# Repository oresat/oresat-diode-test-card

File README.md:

This card tests SWIR LEDs and Photodiodes in space!

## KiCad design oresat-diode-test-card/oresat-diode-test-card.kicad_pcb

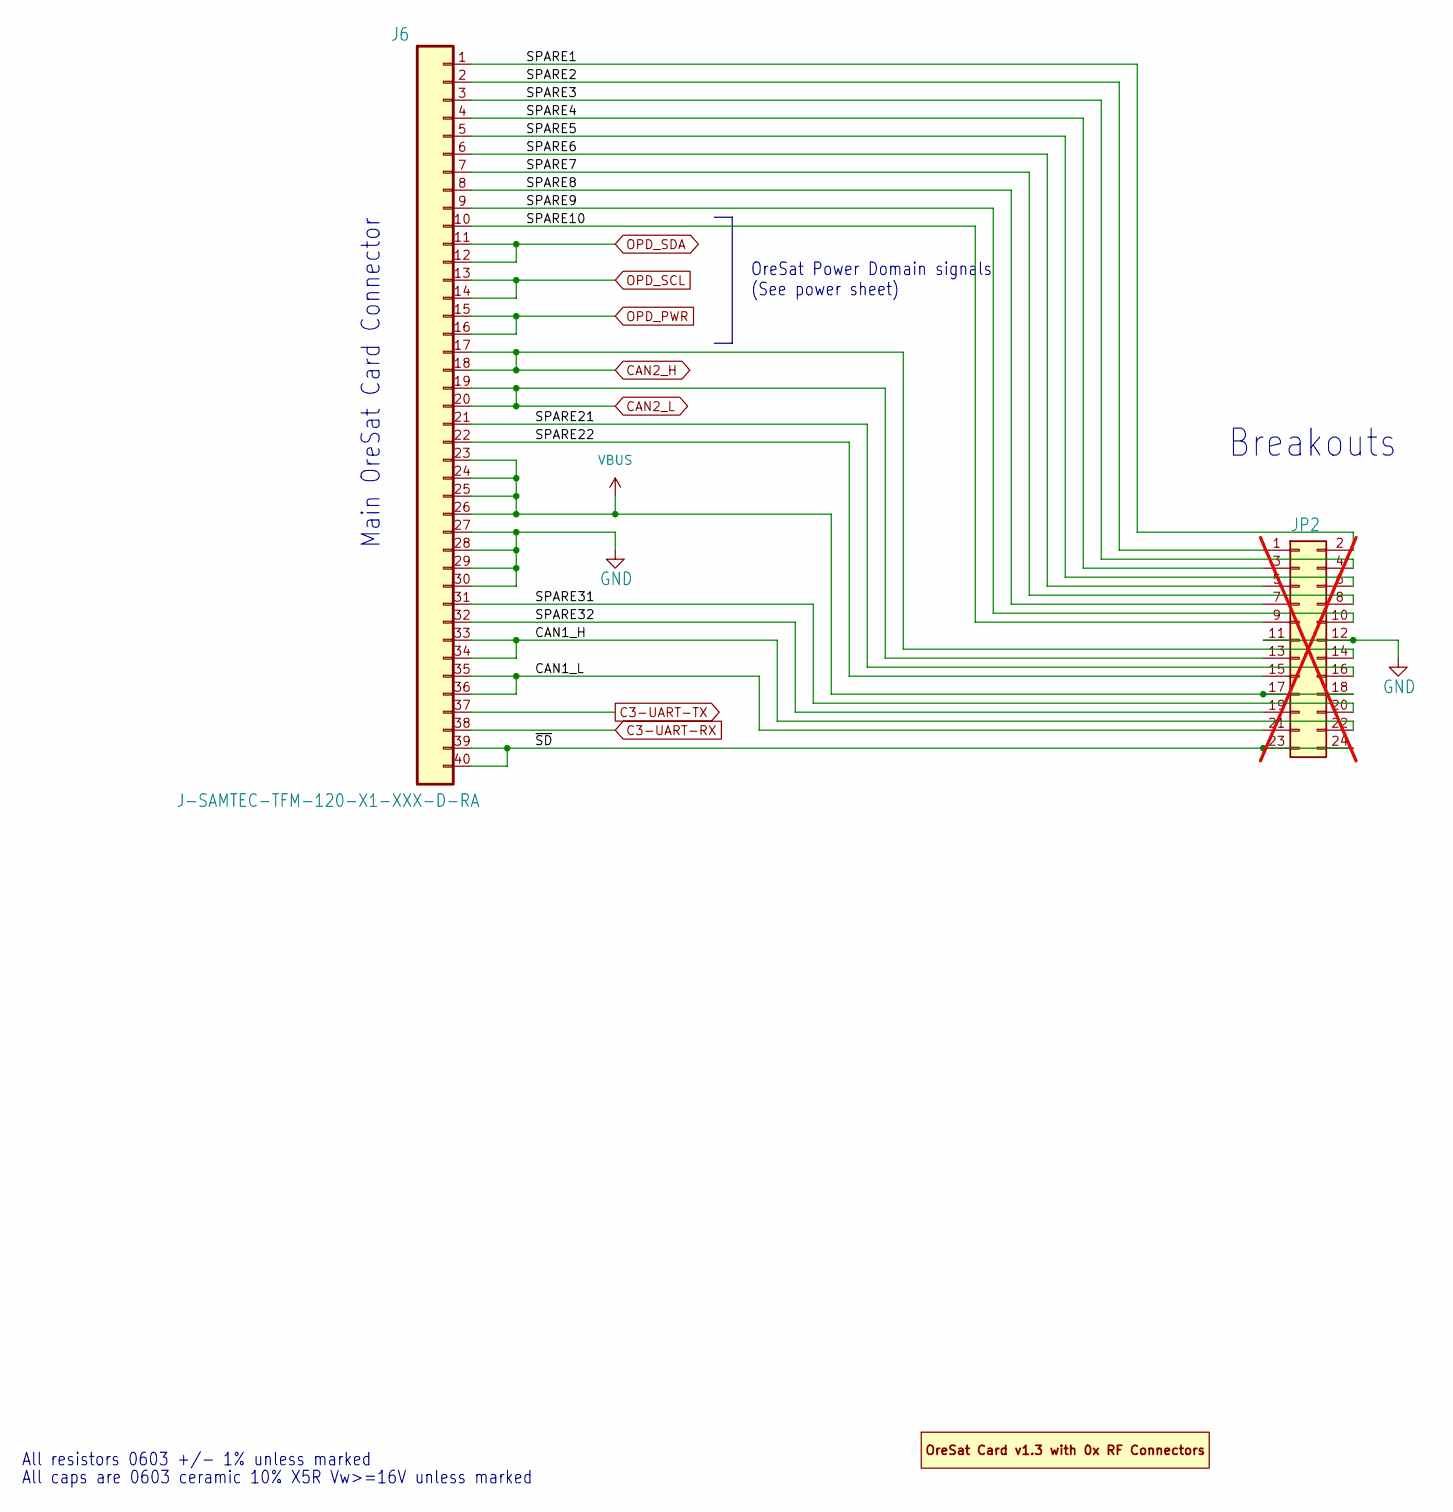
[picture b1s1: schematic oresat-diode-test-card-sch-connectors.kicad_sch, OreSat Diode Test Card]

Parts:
J6: J-SAMTEC-TFM-120-X1-XXX-D-RA; MPN TFM-120-01-L-D-RA
JP2: PINHD-2X12; PinHeader_2x12_P2.54mm_Vertical; MPN N/A; not fitted
PCB1: ORESAT-CARD-V1.0-0xRF; ORESAT-CARD-V1.3-0RF; MPN N/A

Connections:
/Connectors/CAN1_H: J6.33, J6.34, JP2.22
/Connectors/CAN1_L: J6.35, J6.36, JP2.21
/Connectors/SPARE1: J6.1, JP2.2
/Connectors/SPARE2: J6.2, JP2.1
/Connectors/SPARE3: J6.3, JP2.4
/Connectors/SPARE4: J6.4, JP2.3
/Connectors/SPARE5: J6.5, JP2.6
/Connectors/SPARE6: J6.6, JP2.5
/Connectors/SPARE7: J6.7, JP2.8
/Connectors/SPARE8: J6.8, JP2.7
/Connectors/SPARE9: J6.9, JP2.10
/Connectors/SPARE10: J6.10, JP2.9
/Connectors/SPARE21: J6.21, JP2.16
/Connectors/SPARE22: J6.22, JP2.15
/Connectors/SPARE31: J6.31, JP2.20
/Connectors/SPARE32: J6.32, JP2.19
/Connectors/~SD: J6.39, J6.40, JP2.23, JP2.24
C3-UART-RX: J6.38; also elsewhere on the board
C3-UART-TX: J6.37; also elsewhere on the board
CAN2_H: J6.17, J6.18, JP2.14; also elsewhere on the board
CAN2_L: J6.19, J6.20, JP2.13; also elsewhere on the board
GND: J6.27, J6.28, J6.29, J6.30, JP2.11, JP2.12; also elsewhere on the board
OPD_PWR: J6.15, J6.16; also elsewhere on the board
OPD_SCL: J6.13, J6.14; also elsewhere on the board
OPD_SDA: J6.11, J6.12; also elsewhere on the board
VBUS: J6.23, J6.24, J6.25, J6.26, JP2.17, JP2.18; also elsewhere on the board

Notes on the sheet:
Main OreSat Card Connector
Breakouts
All resistors 0603 +/- 1% unless marked
OreSat Power Domain signals (See power sheet)
All caps are 0603 ceramic 10% X5R Vw>=16V unless marked

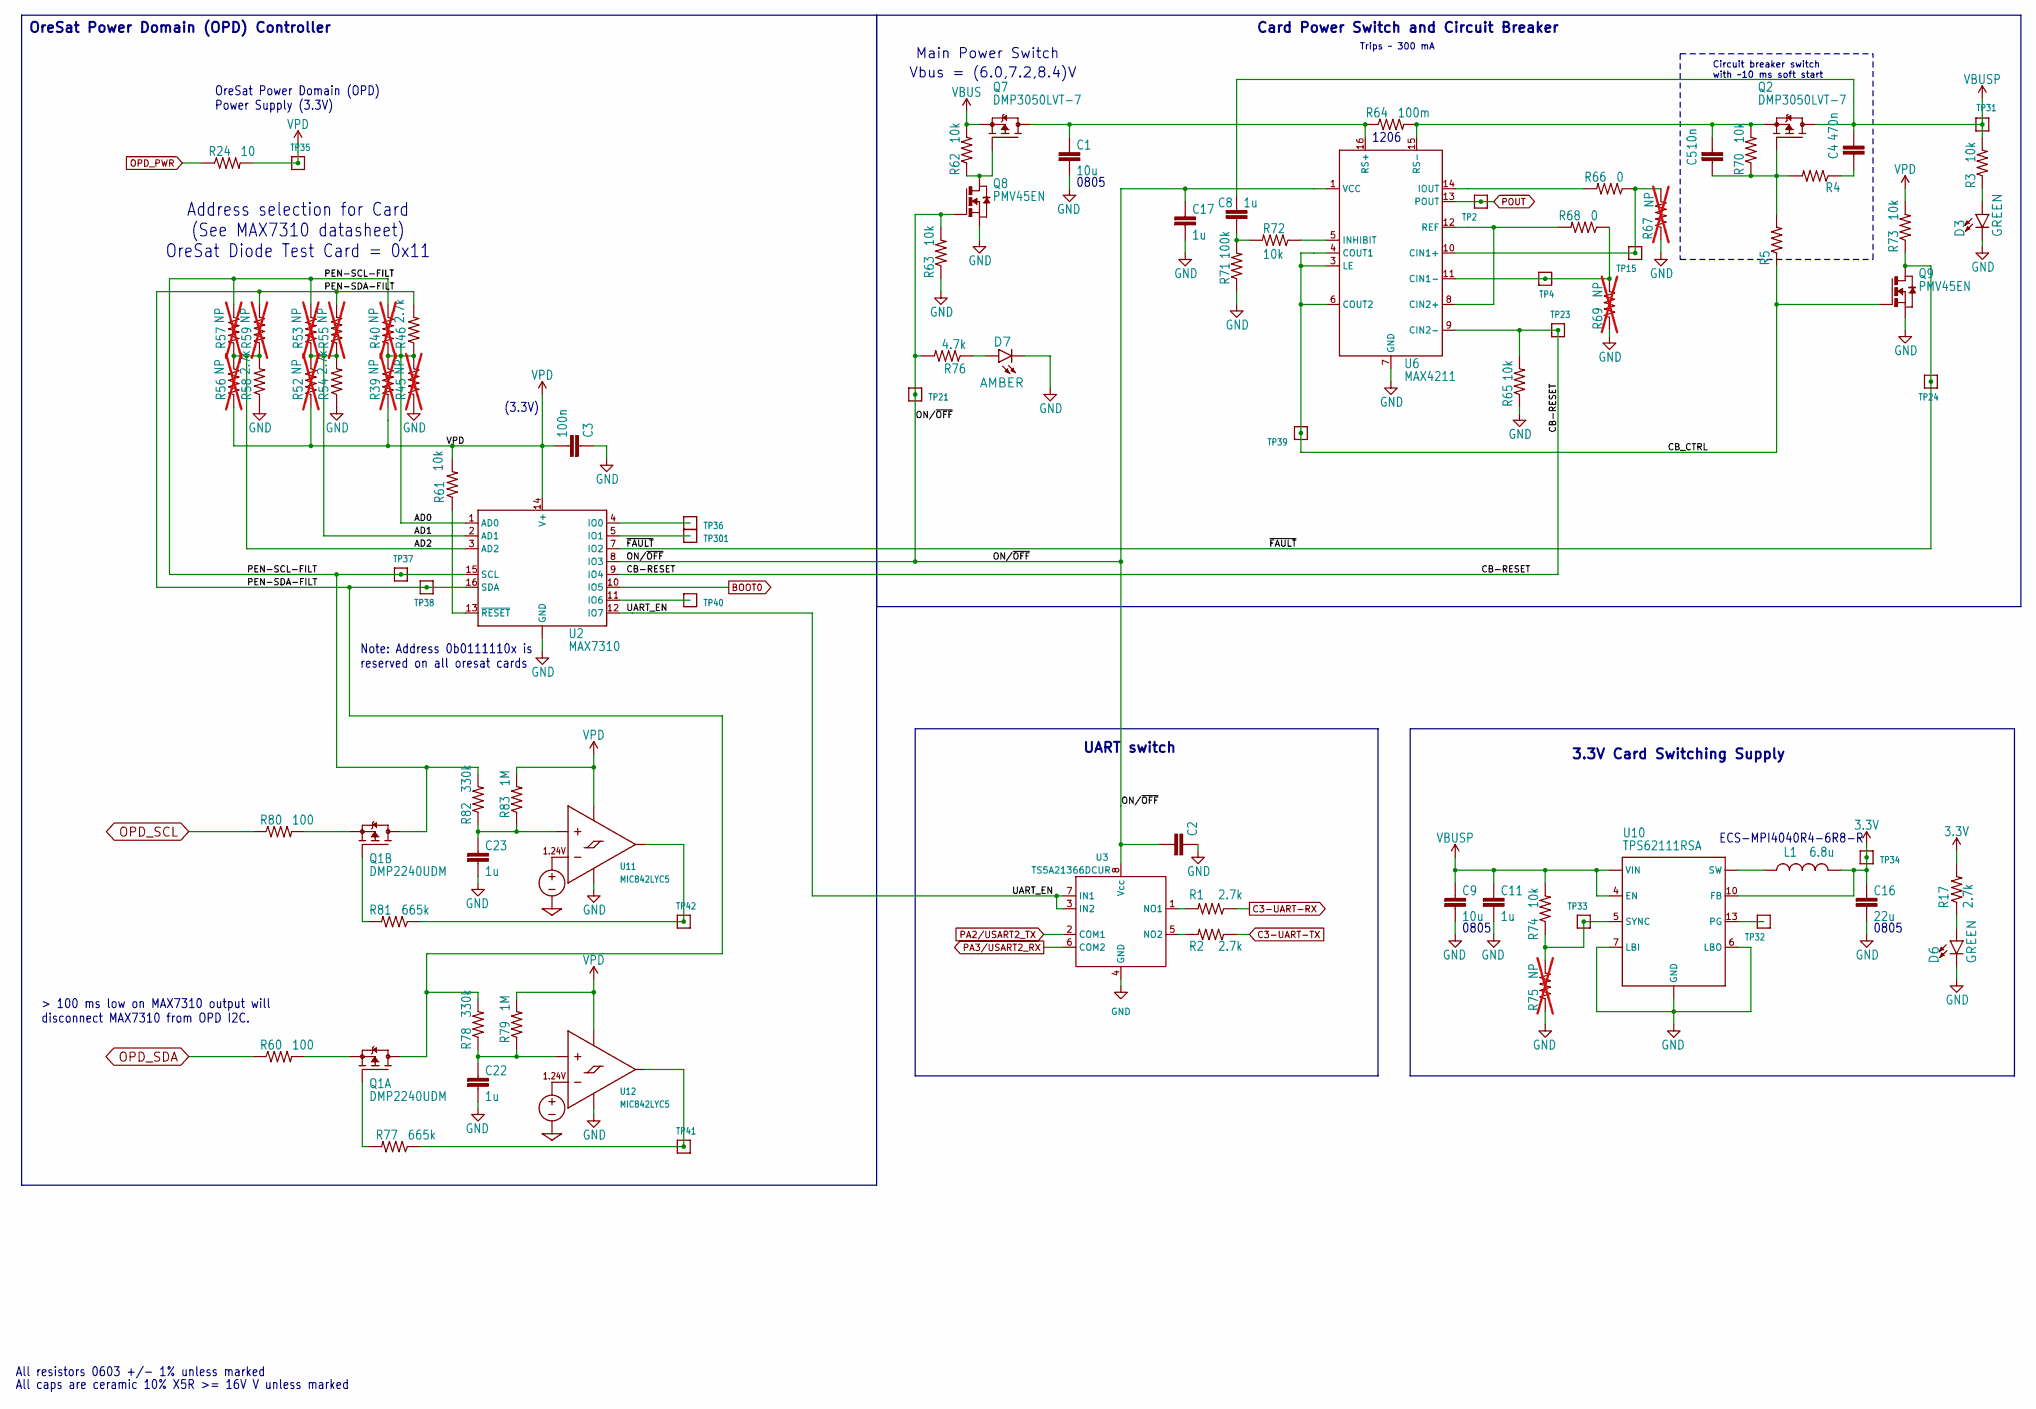
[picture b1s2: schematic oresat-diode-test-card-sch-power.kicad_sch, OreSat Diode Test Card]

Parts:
C1, C9: 10u; 0805-B-NOSILK; MPN GRT21BC71E106KE13L
C2, C3: 100n; 0603-C-NOSILK; MPN TMK107BJ104KAHT
C4: 470n; 0603-C-NOSILK; MPN TMK107BJ474KAHT
C5: 10n; 0603-C-NOSILK; MPN C0603C103J3GECAUTO
C8, C11, C17, C22, C23: 1u; 0603-C-NOSILK; MPN TMK107BJ105KAHT
C16: 22u; 0805-B-NOSILK; MPN GRM21BD71A226ME44L
D3, D6: GREEN; LED-0603; MPN 150060GS75000
D7: AMBER; LED-0603; MPN 150060AS75000
L1: 6.8u; ECS-MPI4040; MPN ECS-MPI4040R4-6R8-R
Q1: DMP2240UDM; SOT23-6; MPN DMP2240UDM
Q2, Q7: DMP3050LVT-7; SOT-23-6; MPN DMP3050LVT-7
Q8, Q9: PMV45EN; SOT-23-3; MPN PMV45EN2R
R1, R2, R17, R46, R54, R58: 2.7k; 0603-C-NOSILK; MPN RMCF0603FT2K70
R3, R4, R5, R61, R62, R63, R65, R70, R72, R73, R74: 10k; 0603-C-NOSILK; MPN RMCF0603FT10K0
R24: 10; 0603-C-NOSILK; MPN RMCF0603FT10R0
R39, R40, R45, R52, R53, R55, R56, R57, R59, R67, R69, R75: NP; 0603-C-NOSILK; MPN RC1005F6653CS; not fitted
R60, R80: 100; 0603-C-NOSILK; MPN RMCF0603FT100R
R64: 100m; R1206; MPN UCR18EVHFLR100
R66, R68: 0; 0603-C-NOSILK; MPN RMCF0603ZT0R00
R71: 100k; 0603-C-NOSILK; MPN RMCF0603FT100K
R76: 4.7k; 0603-C-NOSILK; MPN RMCF0603FT4K70
R77, R81: 665k; 0603-C-NOSILK; MPN RMCF0603FT665K
R78, R82: 330k; 0603-C-NOSILK; MPN RMCF0603FT330K
R79, R83: 1M; 0603-C-NOSILK; MPN RMCF0603FT1M00
TP2, TP4, TP15, TP21, TP23, TP24, TP31, TP32, TP33, TP34, TP35, TP36, TP37, TP38, TP39, TP40, TP41, TP42, TP301: TEST-POINT-LARGE-SQUARE; 1X01; MPN N/A
U2: MAX7310; QFN65P400X400X80-17T210; MPN MAX7310ATE+
U3: TS5A21366DCUR; VSSOP-8_2.3x2mm_P0.5mm; MPN TS5A21366DCUR
U6: MAX4211; QFN-16-1EP_4x4mm_P0.65mm_EP2.1x2.1mm; MPN MAX4211FETE
U10: TPS62111RSA; S-PVQFN-16; MPN TPS62111RSA
U11, U12: MIC842LYC5; SOT-353_SC-70-5; MPN MIC842LYC5-TR

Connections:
3.3V: C16.1, L1.2, R17.2, TP34.1, U10.10 (FB); also elsewhere on the board
/Power/AD0: R39.1, R40.2, R45.2, R46.1, U2.1 (AD0)
/Power/AD1: R52.1, R53.2, R54.2, R55.1, U2.2 (AD1)
/Power/AD2: R56.1, R57.2, R58.2, R59.1, U2.3 (AD2)
/Power/CB-RESET: R65.2, TP23.1, U2.9 (IO4), U6.9 (CIN2-)
/Power/CB_CTRL: Q9.1 (G), R5.1, TP39.1, U6.3 (LE), U6.4 (COUT1), U6.6 (COUT2)
/Power/ON/~OFF: C2.2, C17.1, Q8.1 (G), R63.2, R76.2, TP21.1, U2.8 (IO3), U3.8 (Vcc), U6.1 (VCC)
/Power/PEN-SCL-FILT: Q1.4 (D), R40.1, R53.1, R57.1, R82.2, TP37.1, U2.15 (SCL)
/Power/PEN-SDA-FILT: Q1.6 (D), R46.2, R55.2, R59.2, R78.2, TP38.1, U2.16 (SDA)
/Power/UART_EN: U2.12 (IO7), U3.3 (IN2), U3.7 (IN1)
/Power/~FAULT: Q9.3 (D), R73.1, TP24.1, U2.7 (IO2)
BOOT0: U2.10 (IO5); also elsewhere on the board
C3-UART-RX: R1.1; also elsewhere on the board
C3-UART-TX: R2.1; also elsewhere on the board
GND: C1.2, C2.1, C3.1, C9.2, C11.2, C16.2, C17.2, C22.2, C23.2, D3.C, D6.C, D7.C, Q8.2 (S), Q9.2 (S), R45.1, R54.1, R58.1, R63.1, R65.1, R67.1, R69.1, R71.1, R75.1, U2.6 (GND), U2.EPAD (GND), U3.4 (GND), U6.7 (GND), U6.17 (GND), U10.1 (GND), U10.6 (LBO), U10.7 (LBI), U10.9 (GND), U10.11 (GND), U10.12 (GND), U10.16 (GND), U10.PAD (GND), U11.2 (GND), U12.2 (GND); also elsewhere on the board
unnamed: C4.1, R4.1
unnamed: C8.1, R71.2, R72.2
unnamed: D3.A, R3.1
unnamed: D6.A, R17.1
unnamed: D7.A, R76.1
unnamed: L1.1, U10.14 (SW), U10.15 (SW)
unnamed: Q1.1 (G), R77.2
unnamed: Q1.5 (S), R60.2
unnamed: Q1.3 (G), R81.2
unnamed: Q1.2 (S), R80.2
unnamed: C5.1, Q2.3 (G), R4.2, R5.2, R70.1
unnamed: C5.2, Q2.4 (S), R64.2, R70.2, U6.15 (RS-)
unnamed: Q7.3 (G), Q8.3 (D), R62.1
unnamed: TP36.1, U2.4 (IO0)
unnamed: TP301.1, U2.5 (IO1)
unnamed: TP40.1, U2.11 (IO6)
unnamed: R61.1, U2.13 (~RESET)
unnamed: R1.2, U3.1 (NO1)
unnamed: R2.2, U3.5 (NO2)
unnamed: R66.1, R67.2, TP15.1, U6.10 (CIN1+)
unnamed: R68.1, R69.2, TP4.1, U6.11 (CIN1-)
unnamed: R68.2, U6.8 (CIN2+), U6.12 (REF)
unnamed: R72.1, U6.5 (INHIBIT)
unnamed: R66.2, U6.14 (IOUT)
unnamed: C1.1, Q7.1 (D), Q7.2 (D), Q7.5 (D), Q7.6 (D), R64.1, U6.16 (RS+)
unnamed: TP32.1, U10.13 (PG)
unnamed: R74.1, R75.2, TP33.1, U10.5 (SYNC)
unnamed: C23.1, R82.1, R83.1, U11.1 (INP)
unnamed: R81.1, TP42.1, U11.4 (OUT)
unnamed: C22.1, R78.1, R79.1, U12.1 (INP)
unnamed: R77.1, TP41.1, U12.4 (OUT)
OPD_PWR: R24.1; also elsewhere on the board
OPD_SCL: R80.1; also elsewhere on the board
OPD_SDA: R60.1; also elsewhere on the board
PA2/USART2_TX: U3.2 (COM1); also elsewhere on the board
PA3/USART2_RX: U3.6 (COM2); also elsewhere on the board
POUT: TP2.1, U6.13 (POUT); also elsewhere on the board
VBUS: Q7.4 (S), R62.2; also elsewhere on the board
VBUSP: C4.2, C8.2, C9.1, C11.1, Q2.1 (D), Q2.2 (D), Q2.5 (D), Q2.6 (D), R3.2, R74.2, TP31.1, U10.2 (VIN), U10.3 (VIN), U10.4 (EN), U10.8 (VIN); also elsewhere on the board
VPD: C3.2, R24.2, R39.2, R52.2, R56.2, R61.2, R73.2, R79.2, R83.2, TP35.1, U2.14 (V+), U11.5 (VDD), U12.5 (VDD)

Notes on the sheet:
Card Power Switch and Circuit Breaker
1206
All caps are ceramic 10% X5R >= 16V V unless marked
3.3V Card Switching Supply
Trips ~ 300 mA
Note: Address 0b0111110x is reserved on all oresat cards
> 100 ms low on MAX7310 output will disconnect MAX7310 from OPD I2C.
All resistors 0603 +/- 1% unless marked
OreSat Power Domain (OPD) Power Supply (3.3V)
Vbus = (6.0,7.2,8.4)V
0805
OreSat Power Domain (OPD) Controller
ECS-MPI4040R4-6R8-R
Address selection for Card (See MAX7310 datasheet) OreSat Diode Test Card = 0x11
Circuit breaker switch with ~10 ms soft start
Main Power Switch
UART switch
(3.3V)

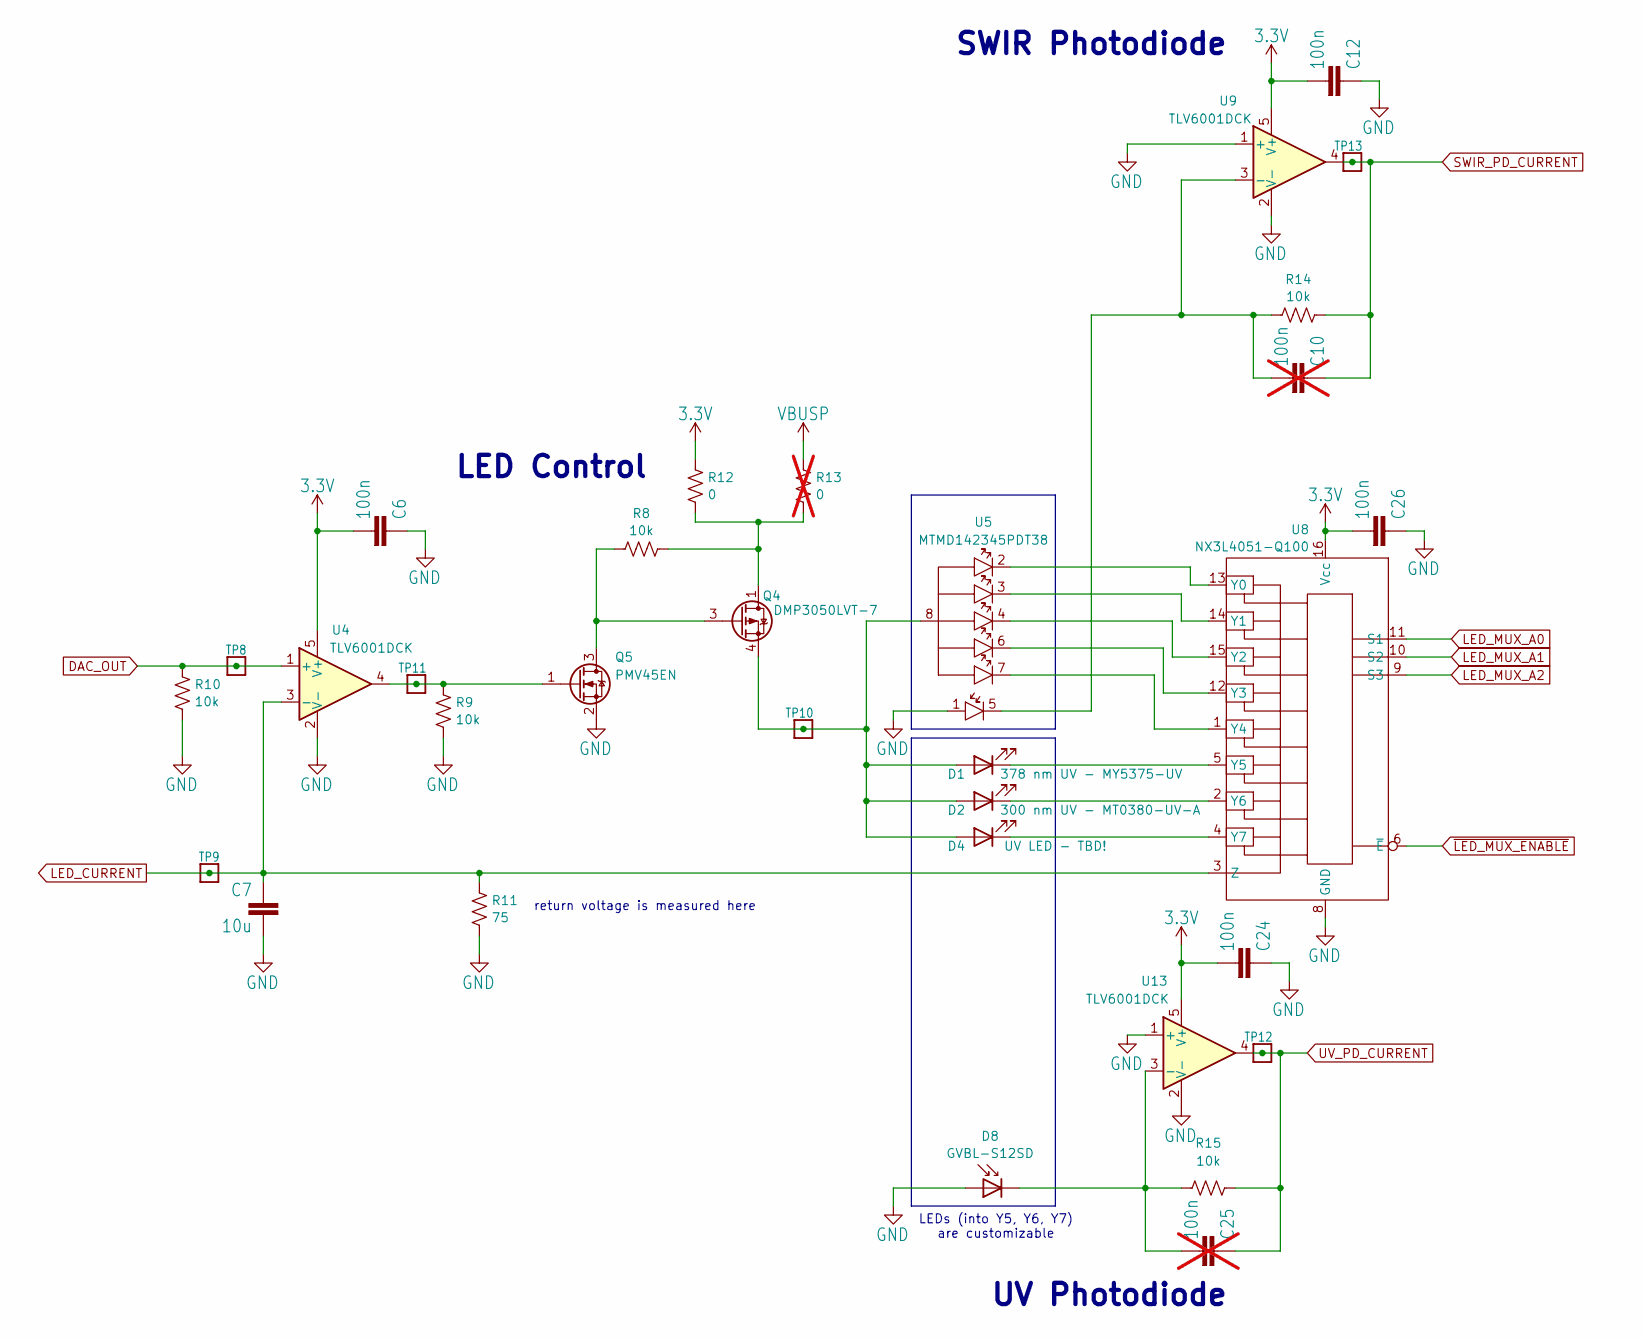
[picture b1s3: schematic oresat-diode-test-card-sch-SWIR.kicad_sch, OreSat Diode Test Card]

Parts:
C6, C12, C24, C26: 100n; 0603-C-NOSILK; MPN TMK107BJ104KAHT
C7: 10u; 0603-C-NOSILK; MPN GRT188R61C106KE13D
C10, C25: 100n; 0603-C-NOSILK; MPN CL05B104KO5NNNC; not fitted
D1: 378 nm UV - MY5375-UV; TO-92-2; MPN MT5375-UV
D2: 300 nm UV - MT0380-UV-A; TO-92-2; MPN MT0380-UV-A
D4: UV LED - TBD!; TO-92-2; MPN N/A
D8: GVBL-S12SD; MPN GVBL-S12SD
Q4: DMP3050LVT-7; SOT-23-6; MPN DMP3050LVT-7
Q5: PMV45EN; SOT-23-3; MPN PMV45EN2R
R8, R9, R10, R14, R15: 10k; 0603-C-NOSILK; MPN RMCF0603FT10K0
R11: 75; 0603-C-NOSILK; MPN RMCF0603FT75R0
R12: 0; 0603-C-NOSILK; MPN RMCF0603ZT0R00
R13: 0; 0603-C-NOSILK; not fitted
TP8, TP9, TP10, TP11, TP12, TP13: TEST-POINT-LARGE-SQUARE; 1X01; MPN N/A
U4, U9, U13: TLV6001DCK; SOT-353_SC-70-5; MPN TLV6001UIDBVR
U5: MTMD142345PDT38; MPN MTMD142345PDT38
U8: NX3L4051-Q100; TSSOP-16_4.4x5mm_P0.65mm; MPN NX3L4051PW-Q100J

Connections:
3.3V: C6.2, C12.2, C24.2, C26.2, R12.2, U4.5 (V+), U8.16 (Vcc), U9.5 (V+), U13.5 (V+); also elsewhere on the board
DAC_OUT: R10.2, TP8.1, U4.1 (+); also elsewhere on the board
GND: C6.1, C7.2, C12.1, C24.1, C26.1, D8.2 (A), Q5.2 (S), R9.1, R10.1, R11.1, U4.2 (V-), U5.1 (PD_Anode), U8.8 (GND), U9.1 (+), U9.2 (V-), U13.1 (+), U13.2 (V-); also elsewhere on the board
LED_CURRENT: C7.1, R11.2, TP9.1, U4.3 (-), U8.3 (Z); also elsewhere on the board
LED_MUX_A0: U8.11 (S1); also elsewhere on the board
LED_MUX_A1: U8.10 (S2); also elsewhere on the board
LED_MUX_A2: U8.9 (S3); also elsewhere on the board
unnamed: D1.2 (A), D2.2 (A), D4.2 (A), Q4.4 (S), TP10.1, U5.8 (LED_Anode_Com)
unnamed: D1.1 (K), U8.5 (Y5)
unnamed: D2.1 (K), U8.2 (Y6)
unnamed: D4.1 (K), U8.4 (Y7)
unnamed: C25.2, D8.1 (K), R15.1, U13.3 (-)
unnamed: Q4.1 (D), Q4.2 (D), Q4.5 (D), Q4.6 (D), R8.2, R12.1, R13.1
unnamed: Q4.3 (G), Q5.3 (D), R8.1
unnamed: Q5.1 (G), R9.2, TP11.1, U4.4
unnamed: U5.2 (1040nm), U8.13 (Y0)
unnamed: U5.3 (1200nm), U8.14 (Y1)
unnamed: U5.4 (1300nm), U8.15 (Y2)
unnamed: U5.6 (1460nm), U8.12 (Y3)
unnamed: U5.7 (1550nm), U8.1 (Y4)
unnamed: C10.2, R14.1, U5.5 (PD_Cathode), U9.3 (-)
SWIR_PD_CURRENT: C10.1, R14.2, TP13.1, U9.4; also elsewhere on the board
UV_PD_CURRENT: C25.1, R15.2, TP12.1, U13.4; also elsewhere on the board
VBUSP: R13.2; also elsewhere on the board
~LED_MUX_ENABLE: U8.6 (~E); also elsewhere on the board

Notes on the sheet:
return voltage is measured here
UV Photodiode
SWIR Photodiode
LEDs (into Y5, Y6, Y7) are customizable
LED Control

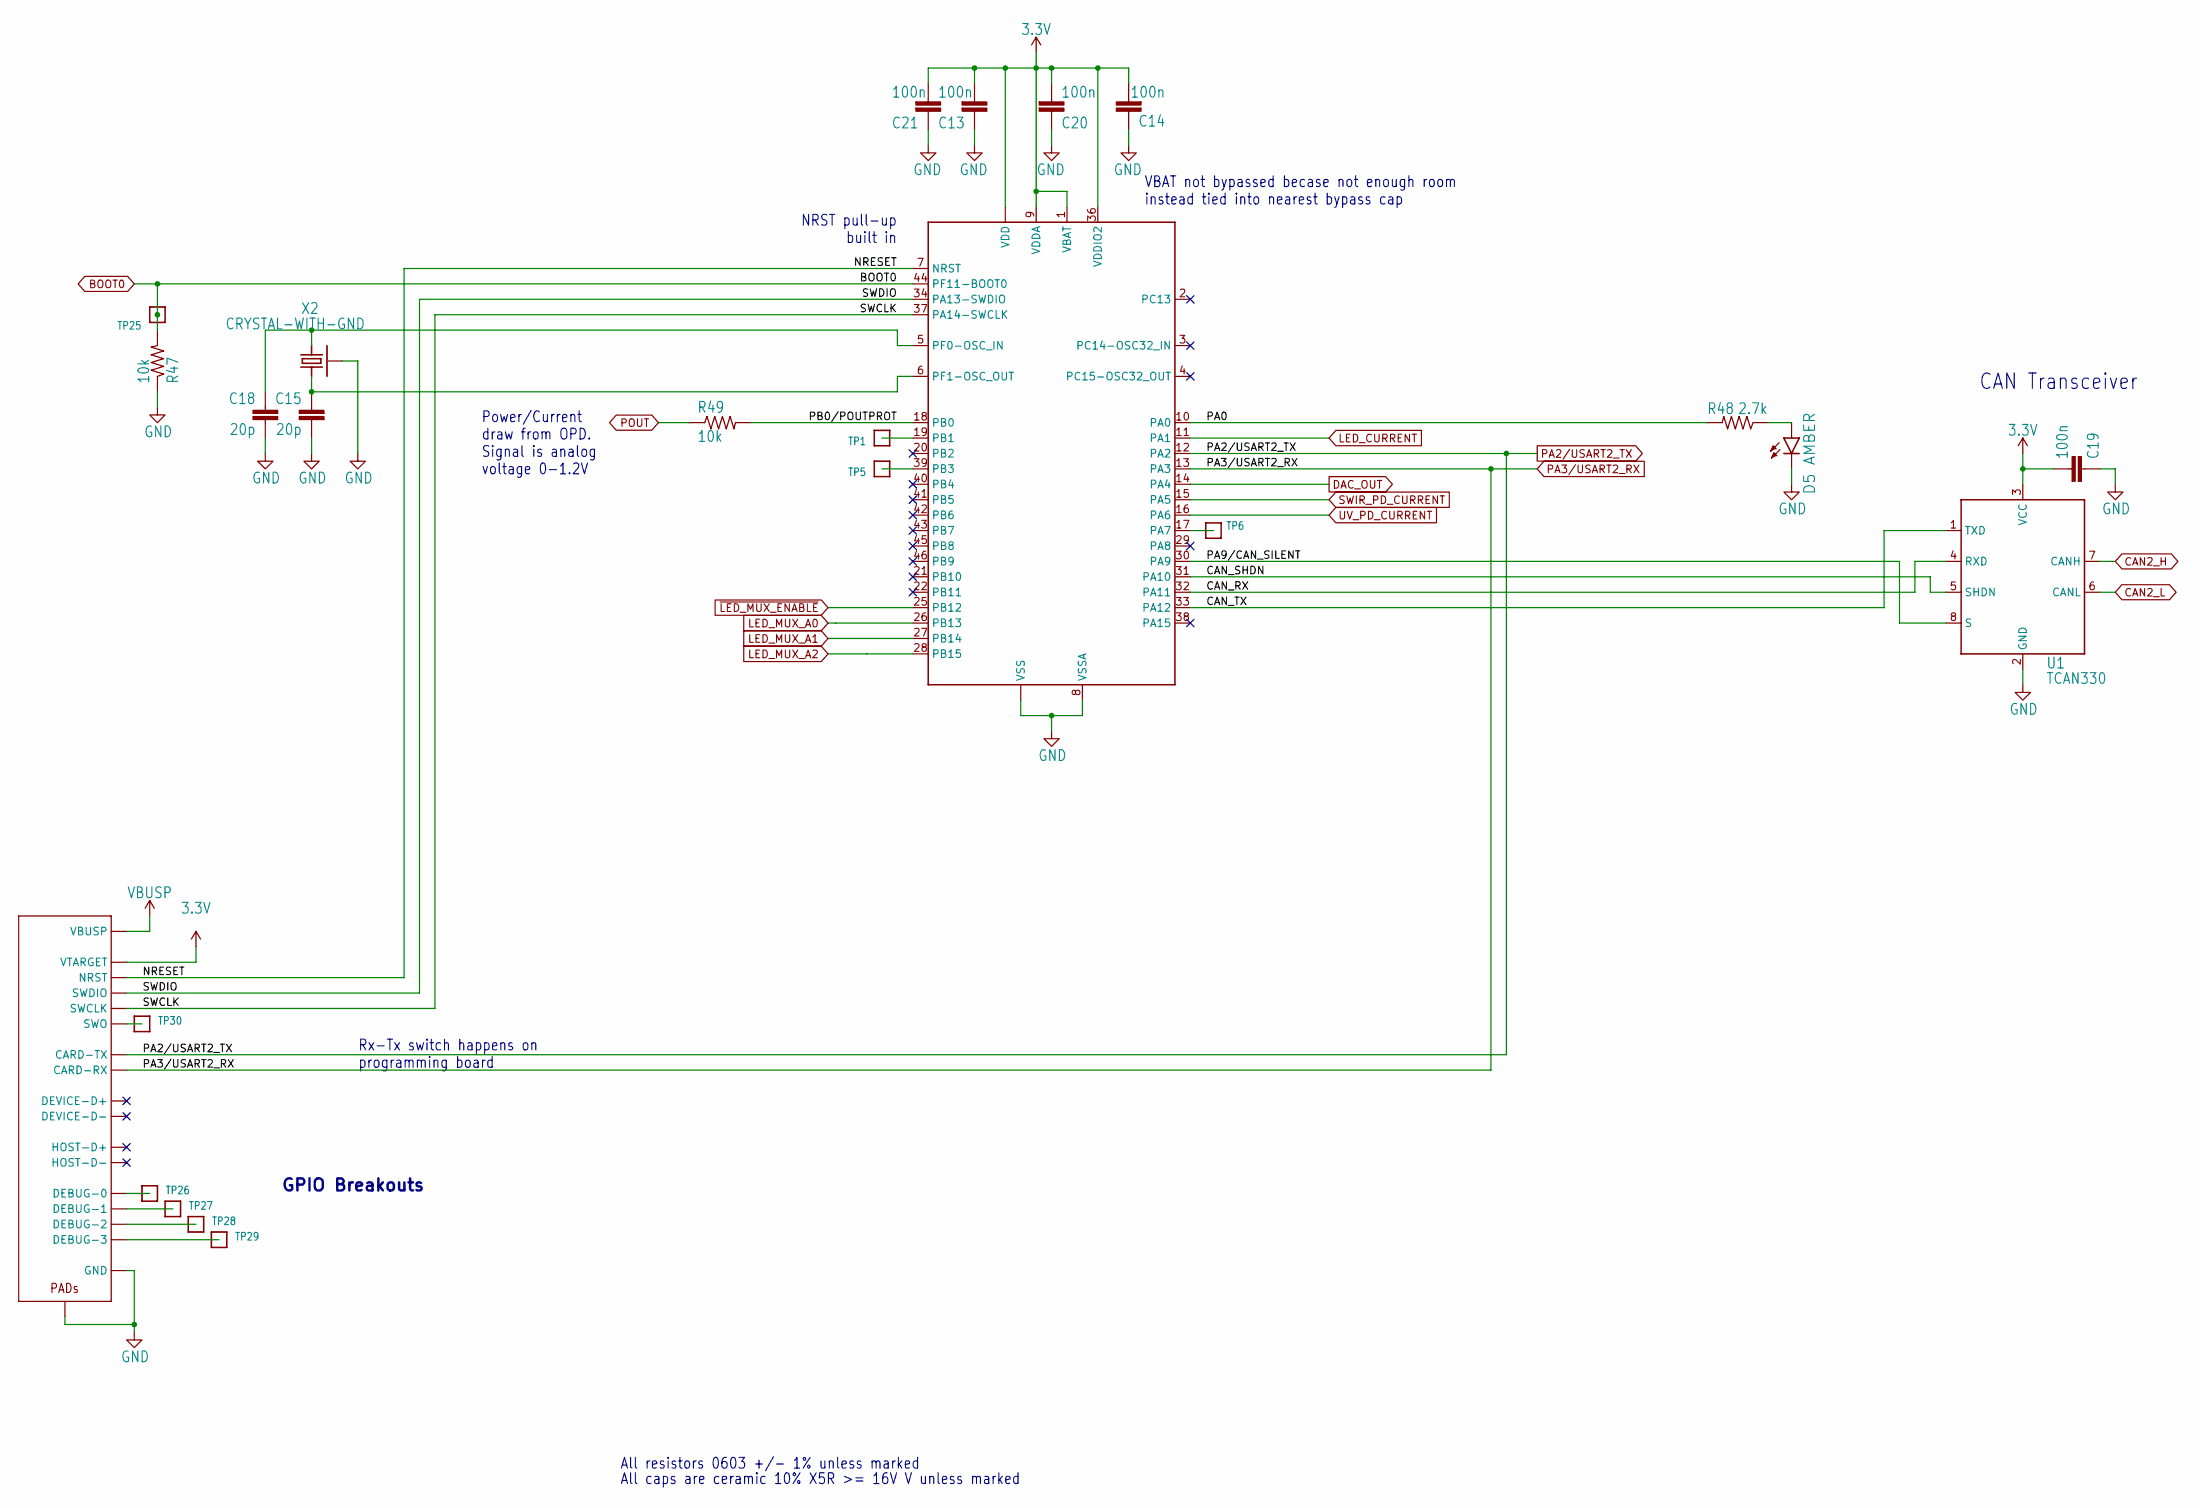
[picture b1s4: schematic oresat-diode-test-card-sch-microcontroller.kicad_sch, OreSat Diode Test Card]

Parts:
C13, C14, C19, C20, C21: 100n; 0603-C-NOSILK; MPN TMK107BJ104KAHT
C15, C18: 20p; 0603-C-NOSILK; MPN GCM1885C2A200JA16D
D5: AMBER; LED-0603; MPN 150060AS75000
J7: ORESAT-DEBUG-CONNECTOR-ALL; TE_2-1734592-0; MPN 2-1734592-0
R47, R49: 10k; 0603-C-NOSILK; MPN RMCF0603FT10K0
R48: 2.7k; 0603-C-NOSILK; MPN RMCF0603FT2K70
TP1, TP5, TP6, TP25, TP26, TP27, TP28, TP29, TP30: TEST-POINT-LARGE-SQUARE; 1X01; MPN N/A
U1: TCAN330; SOT23-8_TI-DCN; MPN TCAN330GDCNT
U7: STM32F091C; MPN STM32F091CCT7
X2: CRYSTAL-WITH-GND; CRYSTAL_2.5X2; MPN ECS-160-10-36Q-ES-TR

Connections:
3.3V: C13.2, C14.2, C19.2, C20.2, C21.2, J7.11 (VTARGET), U1.3 (VCC), U7.1 (VBAT), U7.9 (VDDA), U7.24 (VDD), U7.36 (VDDIO2), U7.48 (VDD); also elsewhere on the board
/Microcontroller/CAN_RX: U1.4 (RXD), U7.32 (PA11)
/Microcontroller/CAN_SHDN: U1.5 (SHDN), U7.31 (PA10)
/Microcontroller/CAN_TX: U1.1 (TXD), U7.33 (PA12)
/Microcontroller/NRESET: J7.10 (NRST), U7.7 (NRST)
/Microcontroller/PA0: R48.2, U7.10 (PA0)
/Microcontroller/PA9/CAN_SILENT: U1.8 (S), U7.30 (PA9)
/Microcontroller/PB0/POUTPROT: R49.2, U7.18 (PB0)
/Microcontroller/SWCLK: J7.15 (SWCLK), U7.37 (PA14-SWCLK)
/Microcontroller/SWDIO: J7.14 (SWDIO), U7.34 (PA13-SWDIO)
BOOT0: R47.2, TP25.1, U7.44 (PF11-BOOT0); also elsewhere on the board
CAN2_H: U1.7 (CANH); also elsewhere on the board
CAN2_L: U1.6 (CANL); also elsewhere on the board
DAC_OUT: U7.14 (PA4); also elsewhere on the board
GND: C13.1, C14.1, C15.2, C18.2, C19.1, C20.1, C21.1, D5.C, J7.3 (GND), J7.6 (GND), J7.9 (GND), J7.PAD1 (PAD), J7.PAD2 (PAD), R47.1, U1.2 (GND), U7.8 (VSSA), U7.23 (VSS), U7.35 (VSS), U7.47 (VSS), X2.2 (SHIELD), X2.4 (SHIELD); also elsewhere on the board
LED_CURRENT: U7.11 (PA1); also elsewhere on the board
LED_MUX_A0: U7.26 (PB13); also elsewhere on the board
LED_MUX_A1: U7.27 (PB14); also elsewhere on the board
LED_MUX_A2: U7.28 (PB15); also elsewhere on the board
unnamed: D5.A, R48.1
unnamed: J7.17 (DEBUG-0), TP26.1
unnamed: J7.18 (DEBUG-1), TP27.1
unnamed: J7.19 (DEBUG-2), TP28.1
unnamed: J7.20 (DEBUG-3), TP29.1
unnamed: J7.16 (SWO), TP30.1
unnamed: TP6.1, U7.17 (PA7)
unnamed: TP1.1, U7.19 (PB1)
unnamed: TP5.1, U7.39 (PB3)
unnamed: C18.1, U7.5 (PF0-OSC_IN), X2.1
unnamed: C15.1, U7.6 (PF1-OSC_OUT), X2.3 (2)
PA2/USART2_TX: J7.13 (CARD-TX), U7.12 (PA2); also elsewhere on the board
PA3/USART2_RX: J7.12 (CARD-RX), U7.13 (PA3); also elsewhere on the board
POUT: R49.1; also elsewhere on the board
SWIR_PD_CURRENT: U7.15 (PA5); also elsewhere on the board
UV_PD_CURRENT: U7.16 (PA6); also elsewhere on the board
VBUSP: J7.1 (VBUSP), J7.2 (VBUSP); also elsewhere on the board
~LED_MUX_ENABLE: U7.25 (PB12); also elsewhere on the board

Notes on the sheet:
Power/Current draw from OPD. Signal is analog voltage 0-1.2V
VBAT not bypassed becase not enough room instead tied into nearest bypass cap
GPIO Breakouts
CAN Transceiver
All resistors 0603 +/- 1% unless marked
All caps are ceramic 10% X5R >= 16V V unless marked
NRST pull-up built in
Rx-Tx switch happens on programming board

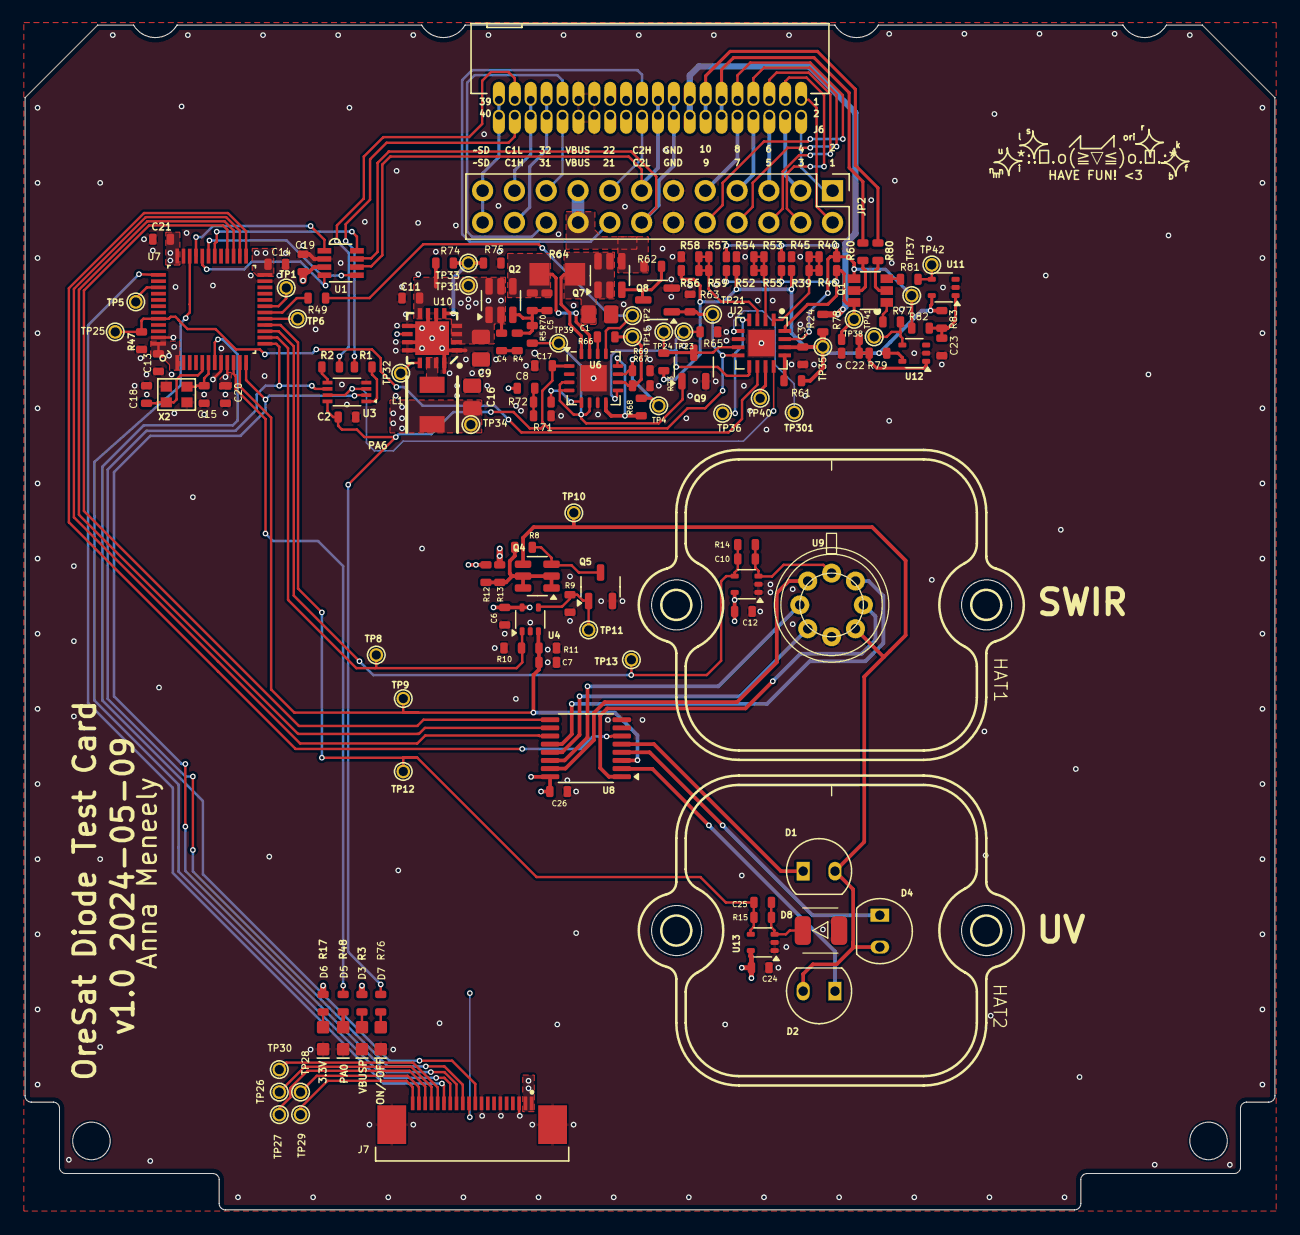
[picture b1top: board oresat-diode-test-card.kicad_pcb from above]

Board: 4 copper layers, 99.8 x 94.6 mm, 150 parts (0 on the bottom side), 116 nets.

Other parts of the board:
HAT1, HAT2: SWIR Diode Cover

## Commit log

2024-04-01 Better ignore
2024-04-01 first check of simulation for constant current source
2024-04-14 moved oresat protocard to diode test card as a starting point.
2024-04-14 added basic schematic for constant current
2024-04-14 added actual files
2024-04-14 added photodiode and mux on schematic
2024-04-20 added additional LED and photodiode slots
2024-04-21 Quick design review on schematic; basically ready for layout.
2024-04-22 Lots of schematic cleanup - replace weird ground and power symbols with more kicad ones, fix values, fix OPD connections and address, update PCB
2024-04-25 started layout of components
2024-04-27 Rename to old directory name
2024-04-27 intial layout placed
2024-05-03 updated UV LED package type
2024-05-05 updated layout and schematic with correct values
2024-05-06 second rought draft layout, fixed library issues
2024-05-07 another layout rev
2024-05-07 Clean up of EAGLE imported ICs, added build directory, moved and locked diode hats.
2024-05-09 latest update
2024-05-10 Fix DRCs, clean up some routing, fix footprint movement on OPD.
2024-05-10 added test points and trace width edits
2024-05-10 Fix OPD weirdness, lots of little polishing including power plane movement and thicker traces.
2024-05-19 Added BOM
2024-05-23 BOM changes! Now up to date.
2024-05-23 Fixed package for op amps :(
